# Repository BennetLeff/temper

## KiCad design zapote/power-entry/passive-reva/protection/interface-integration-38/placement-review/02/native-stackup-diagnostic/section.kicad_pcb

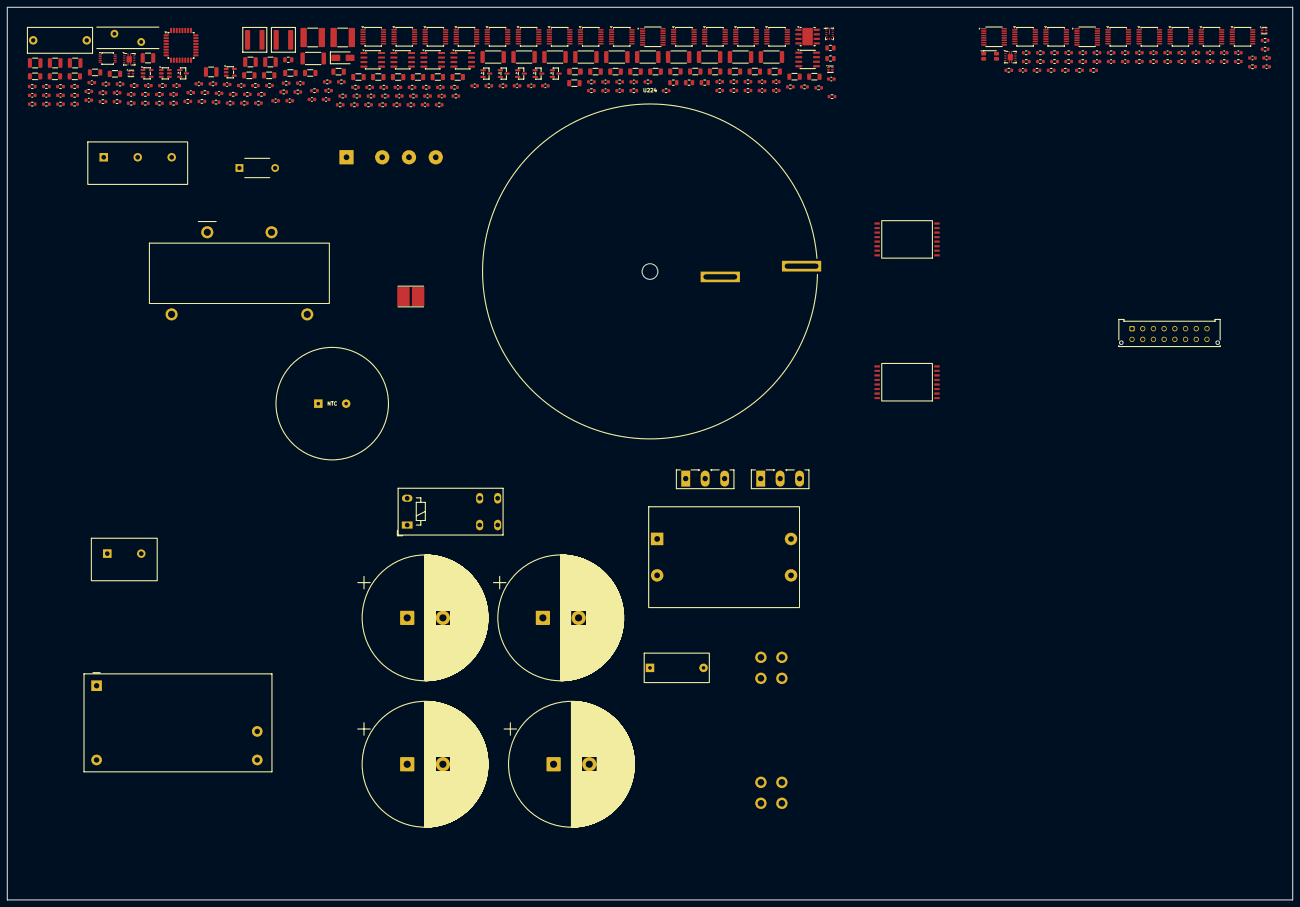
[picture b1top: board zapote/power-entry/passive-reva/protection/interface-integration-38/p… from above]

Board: 6 copper layers, 360.0 x 250.0 mm, 295 parts (0 on the bottom side), 183 nets, no tracks yet.

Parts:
U1: ISO7741FQDWWRQ1; ISO7741FQDWWRQ1_DWW0016A_ReviewOnly
U2: AVR64DA32-E/PT; TQFP-32_7x7mm_P0.8mm
U3, U84: SN74LV221AQPWRQ1; TSSOP-16_4.4x5mm_P0.65mm
U4, U6, U7, U24, U29, U85, U94: SN74HCS74PWR; TSSOP-14_4.4x5mm_P0.65mm
U5, U83: SN74HCS04PWR; TSSOP-14_4.4x5mm_P0.65mm
U8, U10, U11, U15, U19, U22, U25, U27, U30, U31, U32, U41, U45, U46, U47, U48, U49, U80, U110, U111, U112, U113, U114, U115, U116, U117, U118, U119, U122, U124, U132, U140, U144, U145, U172, U175, U176, U187, U196, U198, U257, U277, U280, U295, U296: GRM188R71H104KA93D; C_0603_1608Metric
U9, U12, U16, U17, U20, U23, U28, U33, U34, U35, U37, U39, U42, U43, U50, U51, U52, U53, U54, U55, U56, U57, U58, U59, U60, U62, U63, U64, U65, U66, U67, U68, U69, U70, U71, U74, U75, U79, U81, U86, U88, U90, U95, U96, U97, U98, U99, U100, U101, U102, U103, U104, U105, U106, U107, U108, U109, U121, U131, U135, U139, U143, U171, U186, U289, U291, U292, U293, U294: RC0603FR-0710KL; R_0603_1608Metric
U13, U14, U21, U26, U82, U92, U93, U120, U185: SN74HCS21PWR; TSSOP-14_4.4x5mm_P0.65mm
U18, U87: SN74HCS00PWR; TSSOP-14_4.4x5mm_P0.65mm
U36, U61, U76, U129, U147, U151, U189, U192: RC0603FR-07100KL; R_0603_1608Metric
U38, U40, U89, U91: GRM188R71H103KA01D; C_0603_1608Metric
U44: ISO6742FQDWWRQ1; ISO6742FQDWWRQ1_DWW0016A_ReviewOnly
U72, U137: TPS3431SDRBR; TPS3431SDRBR_DRB0008A_NoVia_ReviewOnly
U73, U138: GRM1885C1H102JA01D; C_0603_1608Metric
U77, U141, U142: TPS389001DSER; WSON-6_1.5x1.5mm_P0.5mm
U78: RC0603FR-0716KL; R_0603_1608Metric
U123: SN74LVC1G06DBVR; SOT-23-5
U125: PMBT3904; SOT-23
U126: RC2512JK-073K3L; R_2512_6332Metric
U127, U148, U152: RC0603FR-0747KL; R_0603_1608Metric
U128: RC1206FR-0710KL; R_1206_3216Metric
U130: UCC27624DDAR; SOIC-8-1EP_3.9x4.9mm_P1.27mm_EP2.95x4.9mm_Mask2.71x3.4mm
U133, U273: GCM31CC71H475KA03L; C_1206_3216Metric
U134: RC1206FR-0710RL; R_1206_3216Metric_Pad1.30x1.75mm_HandSolder
U136: STW65N65DM2AG; TO-247-3_Vertical
U146: RC0603FR-07294KL; R_0603_1608Metric
U149, U153: GRM1885C1H101JA01D; C_0603_1608Metric
U150: RC0603FR-071M02L; R_0603_1608Metric
U154, U155, U156, U157, U162, U163, U164, U165: TNPW1206200KBEEA; R_1206_3216Metric
U158, U166: TNPW1206187KBEEA; R_1206_3216Metric
U159, U167: TNPW1206200RBEEA; R_1206_3216Metric
U160, U168: TNPW12065K62BEEA; R_1206_3216Metric
U161, U169: GRM1885C1H470JA01D; C_0603_1608Metric
U170: LM4040A25IDBZR; SOT-23
U173, U174, U195: TLV3202IDR; SOIC-8_3.9x4.9mm_P1.27mm
U177, U178, U179, U180, U181, U182, U183, U184, U190, U193, U194, U271: RC0603FR-0722KL; R_0603_1608Metric
U188: RC0603FR-07430KL; R_0603_1608Metric
U191: RC0603FR-07560KL; R_0603_1608Metric
U197: SN74LVC1G08DBVR; SOT-23-5
U199: UCC28180D; SOIC-8_3.9x4.9mm_P1.27mm
U200: HCSM2818FT10L0
U201: RC1206FR-07220RL; R_1206_3216Metric
U202: C0805C102J5GACTU; C_0805_2012Metric
U203: BAV23C-E3-08; SOT-23
U204: RC1206FR-0716K2L; R_1206_3216Metric
U205: C0805C272J5GACTU; C_0805_2012Metric
U206: RC1206FR-0740K2L; R_1206_3216Metric
U207: GRM32ER71H475KA88L; C_1210_3225Metric
U208: C0805C224K5RACTU; C_0805_2012Metric
U209: C0805C105K5RACTU; C_0805_2012Metric
U210, U211, U212, U213, U214: CRCW2512200KFKEG; R_2512_6332Metric
U215: RC1206FR-0713KL; R_1206_3216Metric
U216: C0805C681J5GACTU; C_0805_2012Metric
U217, U220, U249: AO3400A; SOT-23
U218, U219, U222, U248: RC1206FR-07100KL; R_1206_3216Metric
U221, U247: RC1206FR-071KL; R_1206_3216Metric
U223: GBJ2510-F; Diode_Bridge_GBJ2510
U224: 760800301; L_Wurth_WE-TORPFC-T75
U225: C3D20065D; TO-247-3_Vertical
U227, U228: 74651173R; Wurth_74651173R_ReviewOnly
U229: B32776P6226K000
U230: B32672P6474K000
U231, U232, U233, U234: LGX2W561MELC50; CP_Radial_D35.0mm_P10.00mm_SnapIn
U235, U236, U237: RC2512FR-07150KL; R_2512_6332Metric
U238: 1714984; Phoenix_1714984
U239: B82726S2163N030; CMC_B82726S
U240: 1714971; Phoenix_1714971
U241: IRM-20-24; Converter_ACDC_MeanWell_IRM-20-xx_THT
U242: SL32 10015; SL32_10015
U243: RT33K012; Relay_SPST_Schrack-RT33K012
U244: B32922C3224M289; C_Rect_L18.0mm_W7.0mm_P15.00mm_FKS3_FKP3
U245: V150LA10AP; RV_Littelfuse_V150LA10AP_D17.0mm_W5.6mm_P7.5mm
U246: VY1102M31Y5UQ63V0; C_Disc_Vishay_VY1102M31Y5UQ63V0
U250: RC2512FK-0791RL; R_2512_6332Metric
U251: SS14; D_SMA
U252: LMR36015BRNXT; Texas_RNX0012C_VQFN-14-11-1EP_2x3mm_P0.5mm_EP0.25x1.825mm
U253, U254: C3225X7R2A106K250AC; C_1210_3225Metric
U255, U256: C3216X7R2A224K115AA; C_1206_3216Metric
U258: C2012X7R1C105K125AA; C_0805_2012Metric
U259: XGL6060-183MEC; L_Coilcraft_XGL6060-XXX
U260, U261: C5750X7R1H226M250KB; C_2220_5750Metric
U262, U284: ERA3AEB104V; R_0603_1608Metric
U263: ERA3AEB7151V; R_0603_1608Metric
U264: LTC4368HMS-2#PBF; LTC4368HMS-2_MSOP10_ReviewOnly
U265: FDS3992; SOIC-8_3.9x4.9mm_P1.27mm
U266: WSL2512R0500FTA; R_2512_6332Metric
U267, U269: TNPU060320K0AWEN00; R_0603_1608Metric
U268: TNPU0603806RAZEN00; R_0603_1608Metric
U270: TNPU0603590RAZEN00; R_0603_1608Metric
U272: GRM188R72A103KA01D; C_0603_1608Metric
U274: TPS54202DDCR; SOT-23-6
U275, U276: C3225X7R1H106K250AC; C_1210_3225Metric
U278: CRCW0603510KJNEA; R_0603_1608Metric
U279: CRCW0603105KFKEA; R_0603_1608Metric
U281: XGL6060-153MEC; L_Coilcraft_XGL6060-XXX
U282, U283: C3225X7R1E226M250AB; C_1210_3225Metric
U285: ERA3AEB1332V; R_0603_1608Metric
U286: GRM1885C1H750JA01D; C_0603_1608Metric
U287: 43045-1612; Molex_Micro-Fit_3.0_43045-1612_2x08_P3.00mm_Vertical
U288: EVQ-P7A01P; SW_SPST_EVQP7A
U290: TCA6408AQPWRQ1; TSSOP-16_4.4x5mm_P0.65mm

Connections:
ac_n: U238.2, U239.2, U244.2, U245.2
ac_rect_l: U223.2, U242.2, U243.3
ac_rect_n: U223.3, U239.3, U241.2
aux15_precut: U259.2, U260.1, U261.1, U262.1, U264.1, U264.6, U265.7, U265.8, U267.1, U269.1
aux_fast_div: U188.2, U189.1, U190.1
aux_fused_l: U240.2, U241.1
aux_ov_div: U191.2, U192.1, U193.1
aux_protected: U126.1, U128.1, U130.6, U132.1, U133.1, U150.1, U188.1, U191.1, U199.7, U209.1, U218.1, U250.1, U264.8, U266.2, U273.1, U274.3, U275.1, U276.1, U277.1, U278.1
aux_window.comparator-out1: U195.1, U197.1
aux_window.comparator-out2: U195.7, U197.2
aux_window.fast_iso-in1_p: U190.2, U195.3
aux_window.ov_iso-in2_n: U193.2, U195.6
aux_window.ov_ref-in2_p: U194.2, U195.5
aux_window_ok: U185.10, U186.1, U197.4
bleed1: U235.2, U236.1
bleed2: U236.2, U237.1
buck_en: U274.5, U278.2, U279.1
buck_vcc: U252.5, U258.1
cext2: U3.6, U40.2
cmc_l_out: U239.4, U240.1, U242.1, U243.4
driver.driver-outa: U130.7, U134.1
driver_first_and: U120.6, U120.9
driver_permission: U120.8, U121.1, U123.2, U221.1
en_shunt_base: U123.4, U125.1, U126.2, U127.1
ena_node: U125.3, U128.2, U129.1, U130.1
f2_detector.cmp_vb-in1_n: U174.2, U182.2
f2_detector.cmp_vb-in1_p: U174.3, U181.2
f2_detector.cmp_vb-in2_n: U174.6, U184.2
f2_detector.cmp_vb-in2_p: U174.5, U183.2
f2_detector.cmp_vb-out1: U174.1, U185.4
f2_detector.cmp_vb-out2: U174.7, U185.5
f2_detector.cmp_vd-in1_n: U173.2, U178.2
f2_detector.cmp_vd-in1_p: U173.3, U177.2
f2_detector.cmp_vd-in2_n: U173.6, U180.2
f2_detector.cmp_vd-in2_p: U173.5, U179.2
f2_detector.cmp_vd-out1: U173.1, U185.1
f2_detector.cmp_vd-out2: U173.7, U185.2
f2_detector.vb_div-high: U166.2, U167.1, U169.1, U182.1, U183.1
f2_detector.vb_div-low: U167.2, U168.1, U180.1
f2_detector.vb_div.r1-p2: U162.2, U163.1
f2_detector.vb_div.r2-p2: U163.2, U164.1
f2_detector.vb_div.r3-p2: U164.2, U165.1
f2_detector.vb_div.r4-p2: U165.2, U166.1
f2_detector.vd_div-high: U158.2, U159.1, U161.1, U178.1, U179.1
f2_detector.vd_div-low: U159.2, U160.1, U184.1
f2_detector.vd_div.r1-p2: U154.2, U155.1
f2_detector.vd_div.r2-p2: U155.2, U156.1
f2_detector.vd_div.r3-p2: U156.2, U157.1
f2_detector.vd_div.r4-p2: U157.2, U158.1
fet_gate: U264.10, U265.1, U265.3, U271.1
fet_source: U265.2, U265.4
freq: U199.4, U204.1
fused_l: U238.1, U239.1, U244.1, U245.1
gate_cap_top: U271.2, U272.1
hot0: U1.9, U1.15, U2.19, U2.29, U3.1, U3.8, U3.9, U4.2, U4.7, U4.11, U4.12, U4.13, U5.7, U5.11, U5.13, U6.7, U6.11, U6.12, U6.13, U7.7, U7.11, U7.12, U7.13, U8.2, U9.2, U10.2, U11.2, U12.2, U13.7, U14.7, U15.2, U16.2, U18.4, U18.5, U18.7, U18.9, U18.10, U18.12, U18.13, U19.2, U20.2, U21.7, U22.2, U23.2, U24.7, U24.11, U24.12, U24.13, U25.2, U26.7, U27.2, U28.2, U29.7, U29.11, U29.12, U29.13, U30.2, U31.2, U32.2, U33.2, U34.2, U35.2, U36.2, U41.2, U42.2, U43.2, U44.9, U44.15, U45.2, U46.2, U48.2, U50.2, U51.2, U52.2, U53.2, U54.2, U55.2, U56.2, U57.2, U61.2, U62.2, U63.2, U64.2, U67.2, U68.2, U69.2, U70.2, U71.2, U120.7, U121.2, U122.2, U123.3, U124.2, U125.2, U127.2, U129.2, U130.3, U130.4, U130.8, U130.9, U131.2, U132.2, U133.2, U135.2, U136.3, U137.4, U137.9, U138.2, U140.2, U141.2, U142.2, U144.2, U145.2, U147.2, U149.2, U151.2, U153.2, U160.2, U161.2, U168.2, U169.2, U170.2, U172.2, U173.4, U174.4, U175.2, U176.2, U185.7, U186.2, U187.2, U189.2, U192.2, U195.4, U196.2, U197.3, U198.2, U199.1, U200.1, U202.2, U203.1, U204.2, U205.2, U207.2, U208.2, U209.2, U215.2, U216.2, U217.2, U219.2, U220.2, U222.2, U229.2, U229.3, U230.2, U231.2, U232.2, U233.2, U234.2, U237.2, U241.3, U246.1, U248.2, U249.2, U252.1, U252.6, U252.8, U252.11, U253.2, U254.2, U255.2, U256.2, U258.2, U260.2, U261.2, U263.2, U264.4, U264.5, U268.2, U270.2, U272.2, U273.2, U274.1, U275.2, U276.2, U277.2, U279.2, U282.2, U283.2, U285.2
hot15_converter-buck_boot: U252.4, U257.1
hot15_converter-buck_fb: U252.7, U262.2, U263.1
hot15_converter-buck_sw: U252.3, U252.12, U257.2, U259.1
hot_abort_asserted: U5.6, U14.12
hot_attempt_valid: U2.4, U13.1, U35.1
hot_aux_ct: U142.5, U153.1
hot_aux_div: U150.2, U151.1, U152.1
hot_aux_sense: U142.1, U152.2
hot_disarm_q: U2.6, U7.5, U14.1, U21.10, U63.1
hot_disarm_sample_request: U2.21, U7.3, U9.1
hot_fault_n: U2.8, U13.10, U62.1, U185.8
hot_history_reset_allowed: U5.9, U14.8, U16.1
hot_history_reset_d: U5.8, U6.2, U17.2
hot_history_reset_raw_n: U3.12, U43.1
hot_history_reset_request: U2.9, U3.10, U68.1
hot_logic5: U1.10, U1.16, U2.18, U2.28, U3.3, U3.11, U3.16, U4.1, U4.10, U4.14, U5.14, U6.1, U6.10, U6.14, U7.4, U7.10, U7.14, U8.1, U10.1, U11.1, U13.13, U13.14, U14.13, U14.14, U15.1, U17.1, U18.14, U19.1, U21.14, U22.1, U24.4, U24.10, U24.14, U25.1, U26.5, U26.12, U26.13, U26.14, U27.1, U29.4, U29.10, U29.14, U30.1, U31.1, U32.1, U37.1, U39.1, U41.1, U44.10, U44.16, U45.1, U46.1, U48.1, U60.1, U65.1, U66.1, U120.14, U122.1, U123.5, U124.1, U137.1, U137.3, U137.5, U139.1, U140.1, U141.3, U141.4, U142.3, U142.4, U143.1, U144.1, U145.1, U146.1, U171.1, U173.8, U174.8, U175.1, U176.1, U185.12, U185.13, U185.14, U187.1, U195.8, U196.1, U197.5, U198.1, U281.2, U282.1, U283.1, U284.1, U286.1
hot_logic5_converter-buck_boot: U274.6, U280.1
hot_logic5_converter-buck_fb: U274.4, U284.2, U285.1, U286.2
hot_logic5_converter-buck_sw: U274.2, U280.2, U281.1
hot_logic_ct: U141.5, U149.1
hot_logic_div: U146.2, U147.1, U148.1
hot_logic_sense: U141.1, U148.2
hot_permit: U1.13, U2.10, U5.1, U26.2, U44.12, U50.1, U120.4
hot_permit_loss_ok: U18.3, U20.1, U21.5
hot_permit_preset_n: U5.2, U6.4, U7.2, U12.1, U14.4, U18.2, U21.12
hot_permit_seen_q: U2.1, U6.5, U18.1, U66.2
hot_prep_abort_ok: U4.6, U14.5, U21.2, U34.1, U120.12
hot_prep_abort_q: U2.7, U4.5, U65.2
hot_prep_reset_raw_n: U3.4, U42.1
hot_prep_reset_request: U2.2, U3.2, U67.1
hot_prep_trip_ok: U4.4, U7.1, U13.8, U14.10, U21.1, U33.1, U120.5
hot_rails_ok: U2.17, U13.5, U61.1, U141.6, U142.6, U143.2
hot_receiver_abort_n: U2.13, U5.5, U21.4, U56.1, U120.10
hot_relay_driver: U2.32, U26.10, U52.1
hot_relay_enable: U26.8, U247.1
hot_relay_request: U1.12, U2.3, U51.1
hot_reset_n: U2.26, U60.2
hot_revalidate_request: U2.14, U24.3, U69.1
hot_run_clear_n: U26.6, U28.1, U29.1, U29.2
hot_run_low: U5.4, U14.2, U21.13
hot_run_q: U2.12, U5.3, U26.9, U29.5, U64.1, U120.1
hot_run_set_request: U2.15, U29.3, U70.1
hot_session_clear_n: U2.20, U21.6, U21.9, U24.1, U26.4, U57.1
hot_session_q: U2.11, U24.5, U26.1, U44.11, U55.1, U120.2
hot_session_revalidate_d: U21.8, U23.1, U24.2
hot_source_health: U13.2, U44.14, U53.1
hot_source_stop_n: U13.4, U44.13, U54.1, U120.13
hot_watchdog_ok: U13.12, U36.1, U137.7, U137.8, U139.2
hot_wd_cwd: U137.2, U138.1
hot_wdi: U2.16, U71.1, U137.6
icomp: U199.2, U205.1
ind: U1.11, U2.30
inhibit_gate: U217.1, U218.2, U219.1, U220.3
isense: U199.3, U201.2, U202.1, U203.3
ov_node: U264.3, U269.2, U270.1
pe: U238.3, U246.2
permit_gate: U220.1, U221.2, U222.1
pfc_control.r_vcomp-p2: U206.2, U207.1
pfc_control.r_vtop1-p2: U210.2, U211.1
pfc_control.r_vtop2-p2: U211.2, U212.1
pfc_control.r_vtop3-p2: U212.2, U213.1
pfc_control.r_vtop4-p2: U213.2, U214.1
pfc_pwm: U130.2, U131.1, U199.8
plus: U223.1, U224.1
raw_aux24: U241.4, U252.2, U252.9, U252.10, U253.1, U254.1, U255.1, U256.1
receiver.history_reset_and-y1: U14.6, U14.9
receiver.iso_protocol-outa: U1.14, U2.31
receiver.prep_trip_and-y1: U13.6, U13.9
receiver.reset_pulses-cext1: U3.14, U38.2
receiver.reset_pulses-q1: U3.13, U4.3
receiver.reset_pulses-q2: U3.5, U6.3
receiver.reset_pulses-rext_cext1: U3.15, U37.2, U38.1
rect_minus: U200.2, U201.1, U223.4
ref25: U170.1, U171.2, U172.1, U177.1, U181.1, U194.1, U195.2
relay_coil_hi: U243.1, U250.2, U251.1
relay_coil_lo: U243.2, U249.3, U251.2
relay_gate: U247.2, U248.1, U249.1
reset_n: U290.3, U291.2
rext_cext2: U3.7, U39.2, U40.1
selv3v3: U1.1, U1.7, U44.1, U44.7, U47.1, U49.1, U72.1, U72.3, U72.5, U74.1, U76.1, U77.3, U77.4, U78.1, U81.1, U82.13, U82.14, U83.14, U84.3, U84.11, U84.16, U85.1, U85.10, U85.14, U86.1, U87.14, U88.1, U90.1, U92.12, U92.13, U92.14, U93.14, U94.4, U94.10, U94.14, U108.1, U110.1, U111.1, U112.1, U113.1, U114.1, U115.1, U116.1, U117.1, U118.1, U119.1, U287.1, U287.9, U289.1, U290.1, U290.16, U291.1, U295.1, U296.1
selv_gnd: U1.2, U1.8, U44.2, U44.8, U47.2, U49.2, U58.2, U59.2, U72.4, U72.9, U73.2, U75.2, U77.2, U79.2, U80.2, U82.7, U83.7, U83.11, U83.13, U84.1, U84.8, U84.9, U85.7, U85.11, U85.12, U85.13, U87.4, U87.5, U87.7, U87.9, U87.10, U87.12, U87.13, U92.7, U93.7, U93.9, U93.10, U93.12, U93.13, U94.7, U94.11, U94.12, U94.13, U95.2, U96.2, U97.2, U98.2, U99.2, U100.2, U101.2, U102.2, U103.2, U104.2, U105.2, U106.2, U107.2, U109.2, U110.2, U111.2, U112.2, U113.2, U114.2, U115.2, U116.2, U117.2, U118.2, U119.2, U287.8, U287.13, U287.16, U288.2, U290.2, U290.8, U292.2, U293.2, U294.2, U295.2, U296.2
sense_upstream: U264.9, U265.5, U265.6, U266.1
source.reset_check-y1: U92.6, U92.9
source.seen_reset_pulse-cext1: U84.14, U91.2
source.seen_reset_pulse-q1: U84.13, U85.3
source.seen_reset_pulse-rext_cext1: U84.15, U90.2, U91.1
source_challenge_active: U92.10, U102.1, U290.4, U292.1
source_clear_n: U93.6, U94.1, U94.2, U106.1
source_command_tx: U1.3, U287.6
source_health_q: U44.3, U82.6, U92.5, U93.1, U104.1
source_hot_permit_fb: U44.5, U58.1, U83.1, U99.1, U290.10
source_hot_session_fb: U44.6, U59.1, U93.4, U98.1, U290.11
source_i2c_scl: U287.12, U290.14
source_i2c_sda: U287.11, U290.15
source_interlock_n: U82.4, U82.10, U96.1, U287.15
source_permit_loss_ok: U87.3, U93.5, U107.1
source_permit_low: U83.4, U92.1
source_permit_q: U1.4, U83.3, U94.5, U103.1, U290.9
source_permit_seen_q: U85.5, U86.2, U87.1, U290.12
source_permit_set_request: U83.5, U94.3, U100.1, U287.4
source_prewatchdog_ok: U82.8, U105.1, U287.5
source_rail_ct: U77.5, U80.1
source_rail_reset_n: U77.6, U81.2, U82.5, U82.12, U290.7
source_rail_sense: U77.1, U78.2, U79.1
source_relay_request: U1.5, U290.6, U294.1
source_reset_good: U82.1, U82.9, U95.1, U287.14
source_response_rx: U1.6, U287.7
source_seen_preset_n: U83.2, U85.4, U87.2, U92.2, U109.1
source_seen_reset_allowed: U83.9, U92.8
source_seen_reset_d: U83.8, U85.2, U108.2
source_seen_reset_request: U84.2, U101.1, U290.5, U293.1
source_set_low: U83.6, U92.4
source_start_n: U287.10, U288.1, U289.2
source_stop_n: U44.4, U93.2, U97.1, U287.2
source_validated_heartbeat: U75.1, U84.10, U287.3
source_watchdog_good: U72.7, U72.8, U74.2, U82.2
source_wd_cwd: U72.2, U73.1
source_wdi: U72.6, U76.2, U84.12
source_wdi_cext: U84.6, U89.2
source_wdi_rext_cext: U84.7, U88.2, U89.1
stw_drain: U136.2, U224.2, U225.1, U225.3
stw_gate: U134.2, U135.1, U136.1
uv_node: U264.2, U267.2, U268.1
vb_bank: U162.1, U228.1, U231.1, U232.1, U233.1, U234.1, U235.1
vcomp: U199.5, U206.1, U208.1
vd_local: U154.1, U210.1, U225.2, U227.1, U229.1, U229.4, U230.1
vdvb_health: U185.6, U185.9
vsense_node: U199.6, U214.2, U215.1, U216.1, U217.3
